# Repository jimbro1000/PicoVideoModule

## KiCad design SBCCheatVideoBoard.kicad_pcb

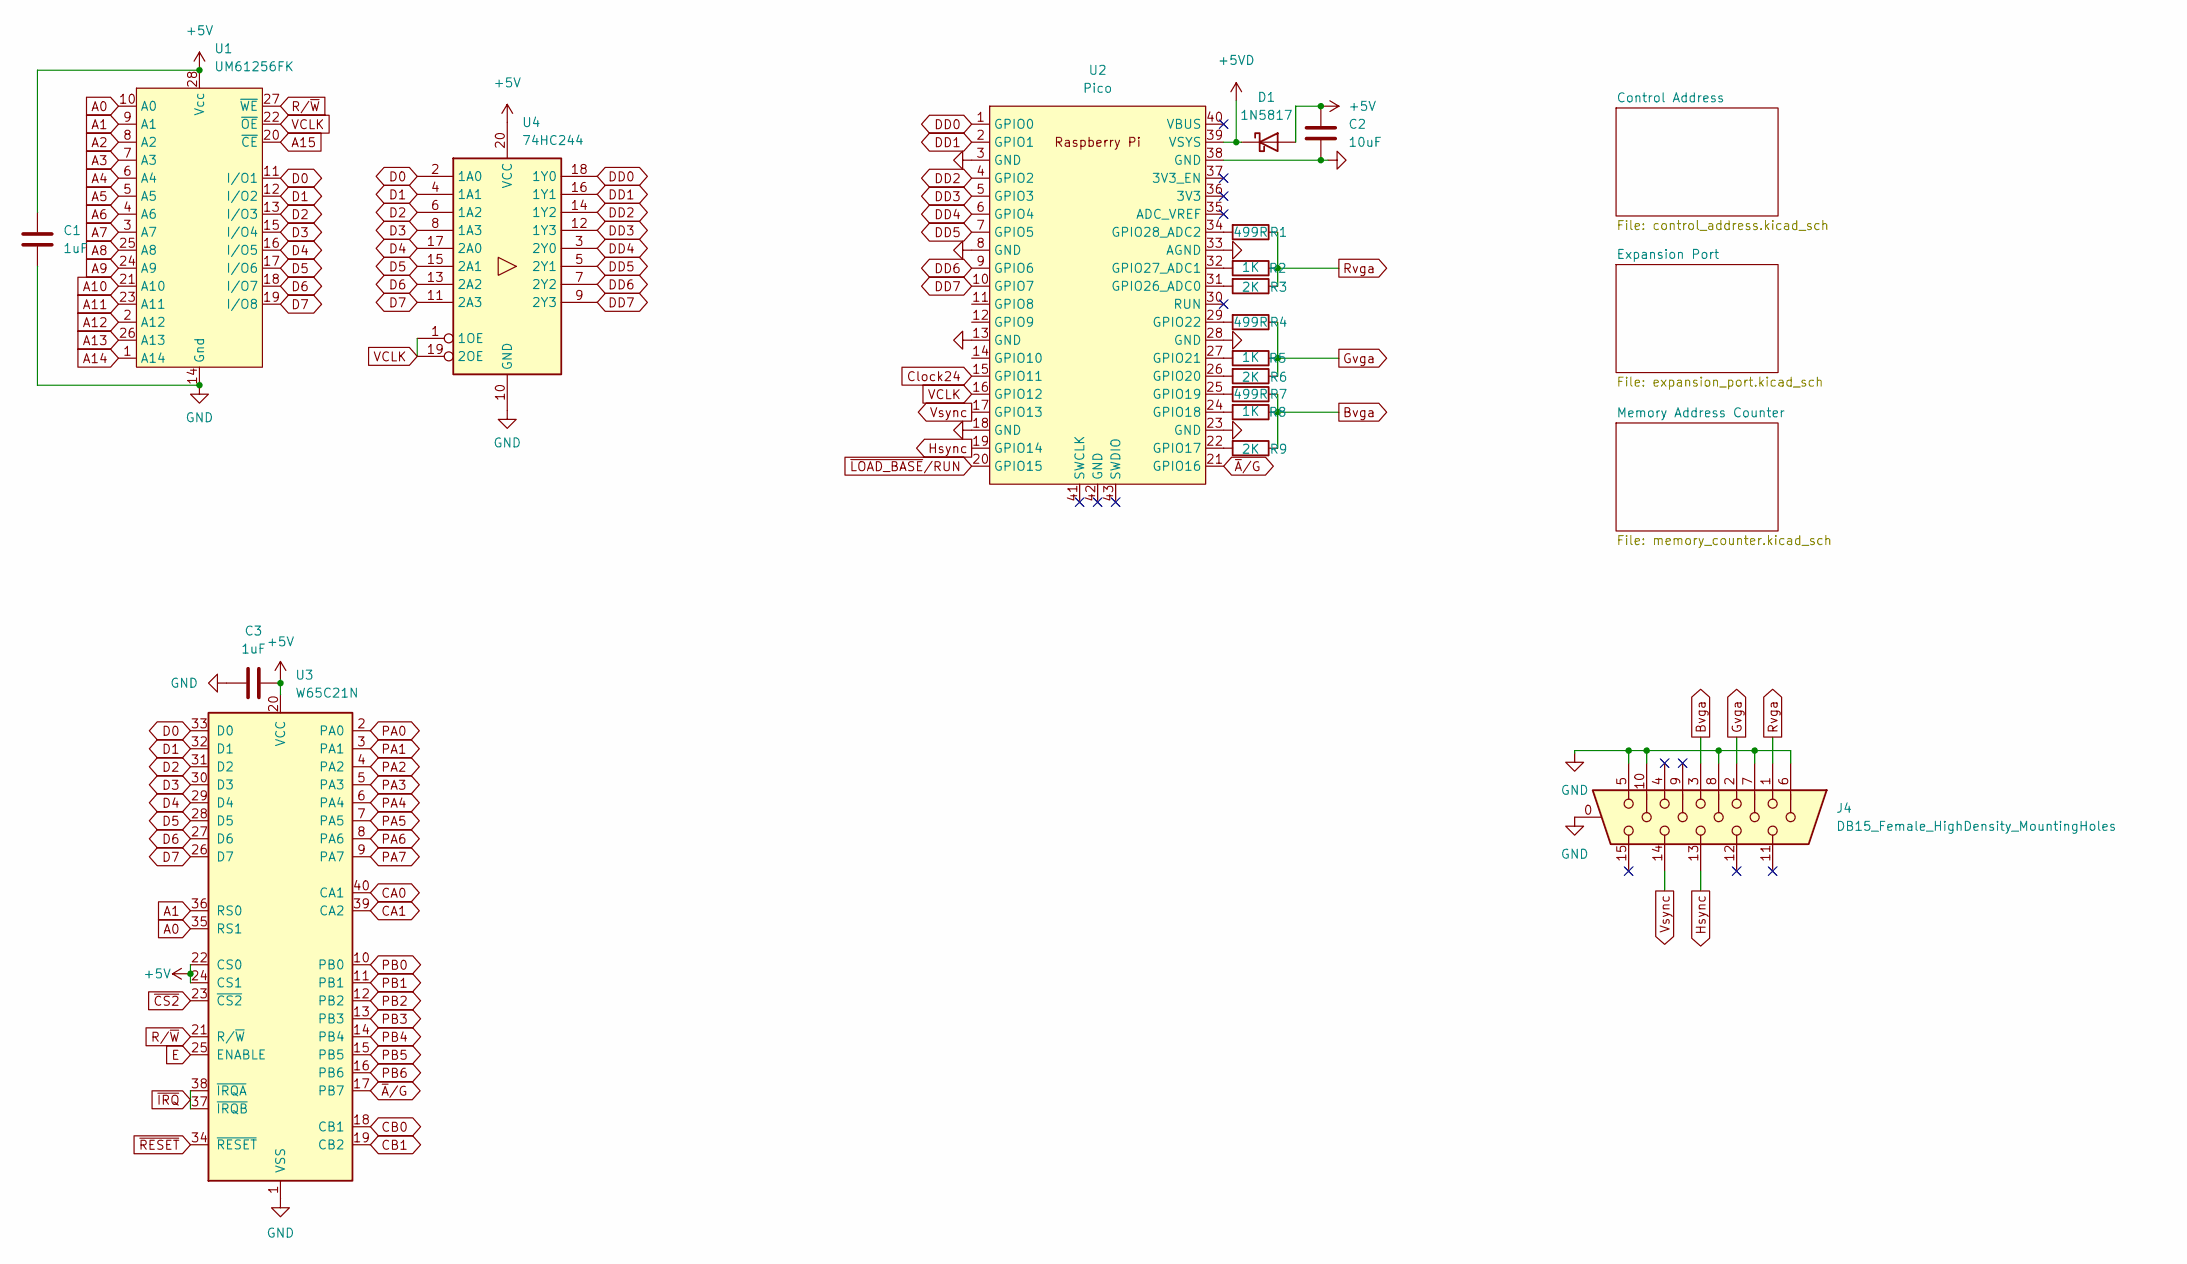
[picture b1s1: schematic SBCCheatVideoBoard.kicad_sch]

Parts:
C1, C3: 1uF; C_0805_2012Metric
C2: 10uF; C_0805_2012Metric
D1: 1N5817; D_SOD-523
J4: DB15_Female_HighDensity_MountingHoles; DSUB-15-HD_Female_Horizontal_P2.29x1.98mm_EdgePinOffset3.03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
R1, R4, R7: 499R; R_0805_2012Metric
R2, R5, R8: 1K; R_0805_2012Metric
R3, R6, R9: 2K; R_0805_2012Metric
U1: UM61256FK; DIP-28_W7.62mm
U2: Pico; DIP-40_W15.24mm
U3: W65C21N; DIP-40_W15.24mm
U4: 74HC244; SO-20_5.3x12.6mm_P1.27mm

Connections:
+5V: C1.1, C2.1, C3.1, D1.2 (A), U1.28 (Vcc), U3.20 (VCC), U3.22 (CS0), U3.24 (CS1), U4.20 (VCC); also elsewhere on the board
+5VD: D1.1 (K), U2.39 (VSYS)
A0: U1.10 (A0), U3.35 (RS1); also elsewhere on the board
A1: U1.9 (A1), U3.36 (RS0); also elsewhere on the board
A2: U1.8 (A2); also elsewhere on the board
A3: U1.7 (A3); also elsewhere on the board
A4: U1.6 (A4); also elsewhere on the board
A5: U1.5 (A5); also elsewhere on the board
A6: U1.4 (A6); also elsewhere on the board
A7: U1.3 (A7); also elsewhere on the board
A8: U1.25 (A8); also elsewhere on the board
A9: U1.24 (A9); also elsewhere on the board
A10: U1.21 (A10); also elsewhere on the board
A11: U1.23 (A11); also elsewhere on the board
A12: U1.2 (A12); also elsewhere on the board
A13: U1.26 (A13); also elsewhere on the board
A14: U1.1 (A14); also elsewhere on the board
A15: U1.20 (~CE); also elsewhere on the board
Bvga: J4.3, R7.1, R8.1, R9.1
CA0: U3.40 (CA1)
CA1: U3.39 (CA2)
CB0: U3.18 (CB1)
CB1: U3.19 (CB2)
Clock24: U2.15 (GPIO11); also elsewhere on the board
D0: U1.11 (I/O1), U3.33 (D0), U4.2 (1A0); also elsewhere on the board
D1: U1.12 (I/O2), U3.32 (D1), U4.4 (1A1); also elsewhere on the board
D2: U1.13 (I/O3), U3.31 (D2), U4.6 (1A2); also elsewhere on the board
D3: U1.15 (I/O4), U3.30 (D3), U4.8 (1A3); also elsewhere on the board
D4: U1.16 (I/O5), U3.29 (D4), U4.17 (2A0); also elsewhere on the board
D5: U1.17 (I/O6), U3.28 (D5), U4.15 (2A1); also elsewhere on the board
D6: U1.18 (I/O7), U3.27 (D6), U4.13 (2A2); also elsewhere on the board
D7: U1.19 (I/O8), U3.26 (D7), U4.11 (2A3); also elsewhere on the board
DD0: U2.1 (GPIO0), U4.18 (1Y0)
DD1: U2.2 (GPIO1), U4.16 (1Y1)
DD2: U2.4 (GPIO2), U4.14 (1Y2)
DD3: U2.5 (GPIO3), U4.12 (1Y3)
DD4: U2.6 (GPIO4), U4.3 (2Y0)
DD5: U2.7 (GPIO5), U4.5 (2Y1)
DD6: U2.9 (GPIO6), U4.7 (2Y2)
DD7: U2.10 (GPIO7), U4.9 (2Y3)
E: U3.25 (ENABLE); also elsewhere on the board
GND: C1.2, C2.2, C3.2, J4.0, J4.5, J4.6, J4.7, J4.8, J4.10, U1.14 (Gnd), U2.3 (GND), U2.8 (GND), U2.13 (GND), U2.18 (GND), U2.23 (GND), U2.28 (GND), U2.33 (AGND), U2.38 (GND), U3.1 (VSS), U4.10 (GND); also elsewhere on the board
Gvga: J4.2, R4.1, R5.1, R6.1
Hsync: J4.13, U2.19 (GPIO14)
unnamed: R1.2, U2.34 (GPIO28_ADC2)
unnamed: R2.2, U2.32 (GPIO27_ADC1)
unnamed: R3.2, U2.31 (GPIO26_ADC0)
unnamed: R4.2, U2.29 (GPIO22)
unnamed: R5.2, U2.27 (GPIO21)
unnamed: R6.2, U2.26 (GPIO20)
unnamed: R7.2, U2.25 (GPIO19)
unnamed: R8.2, U2.24 (GPIO18)
unnamed: R9.2, U2.22 (GPIO17)
PA0: U3.2 (PA0); also elsewhere on the board
PA1: U3.3 (PA1); also elsewhere on the board
PA2: U3.4 (PA2); also elsewhere on the board
PA3: U3.5 (PA3); also elsewhere on the board
PA4: U3.6 (PA4); also elsewhere on the board
PA5: U3.7 (PA5); also elsewhere on the board
PA6: U3.8 (PA6); also elsewhere on the board
PA7: U3.9 (PA7); also elsewhere on the board
PB0: U3.10 (PB0); also elsewhere on the board
PB1: U3.11 (PB1); also elsewhere on the board
PB2: U3.12 (PB2); also elsewhere on the board
PB3: U3.13 (PB3)
PB4: U3.14 (PB4)
PB5: U3.15 (PB5)
PB6: U3.16 (PB6)
Rvga: J4.1, R1.1, R2.1, R3.1
R/~W: U1.27 (~WE), U3.21 (R/~W); also elsewhere on the board
VCLK: U1.22 (~OE), U2.16 (GPIO12), U4.1 (1OE), U4.19 (2OE); also elsewhere on the board
Vsync: J4.14, U2.17 (GPIO13)
~A/G: U2.21 (GPIO16), U3.17 (PB7)
~CS2: U3.23 (~CS2); also elsewhere on the board
~IRQ: U3.37 (~IRQB), U3.38 (~IRQA); also elsewhere on the board
~LOAD_BASE/RUN: U2.20 (GPIO15); also elsewhere on the board
~RESET: U3.34 (~RESET); also elsewhere on the board

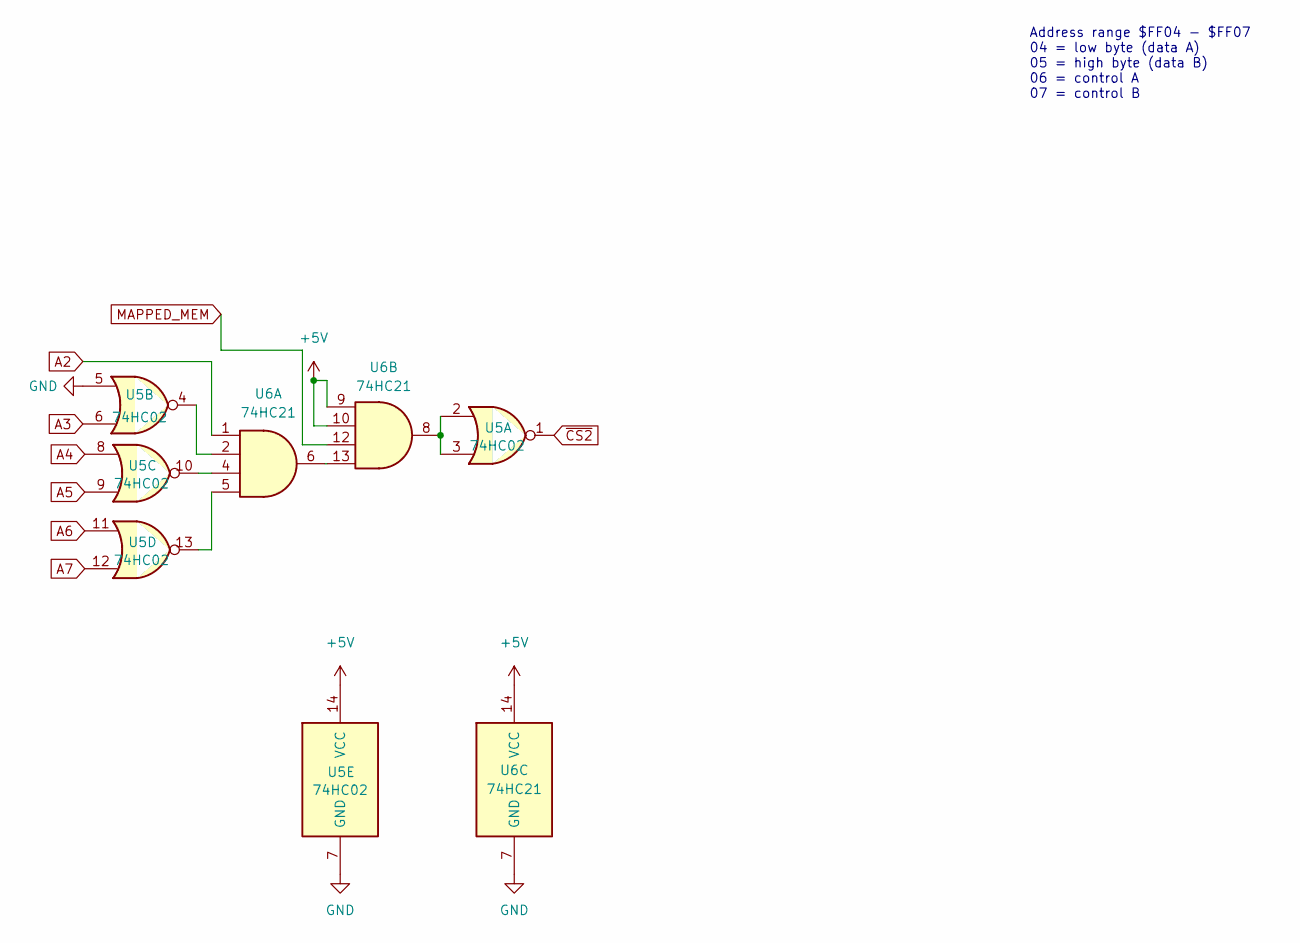
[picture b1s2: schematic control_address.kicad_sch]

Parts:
U5: 74HC02; SO-14_3.9x8.65mm_P1.27mm
U6: 74HC21; SO-14_3.9x8.65mm_P1.27mm

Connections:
+5V: U5.14 (VCC), U6.9, U6.10, U6.14 (VCC); also elsewhere on the board
A2: U6.1; also elsewhere on the board
A3: U5.6; also elsewhere on the board
A4: U5.8; also elsewhere on the board
A5: U5.9; also elsewhere on the board
A6: U5.11; also elsewhere on the board
A7: U5.12; also elsewhere on the board
GND: U5.5, U5.7 (GND), U6.7 (GND); also elsewhere on the board
MAPPED_MEM: U6.12; also elsewhere on the board
unnamed: U5.2, U5.3, U6.8
unnamed: U5.4, U6.2
unnamed: U5.10, U6.4
unnamed: U5.13, U6.5
unnamed: U6.6, U6.13
~CS2: U5.1; also elsewhere on the board

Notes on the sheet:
Address range $FF04 - $FF07 04 = low byte (data A) 05 = high byte (data B) 06 = control A 07 = control B

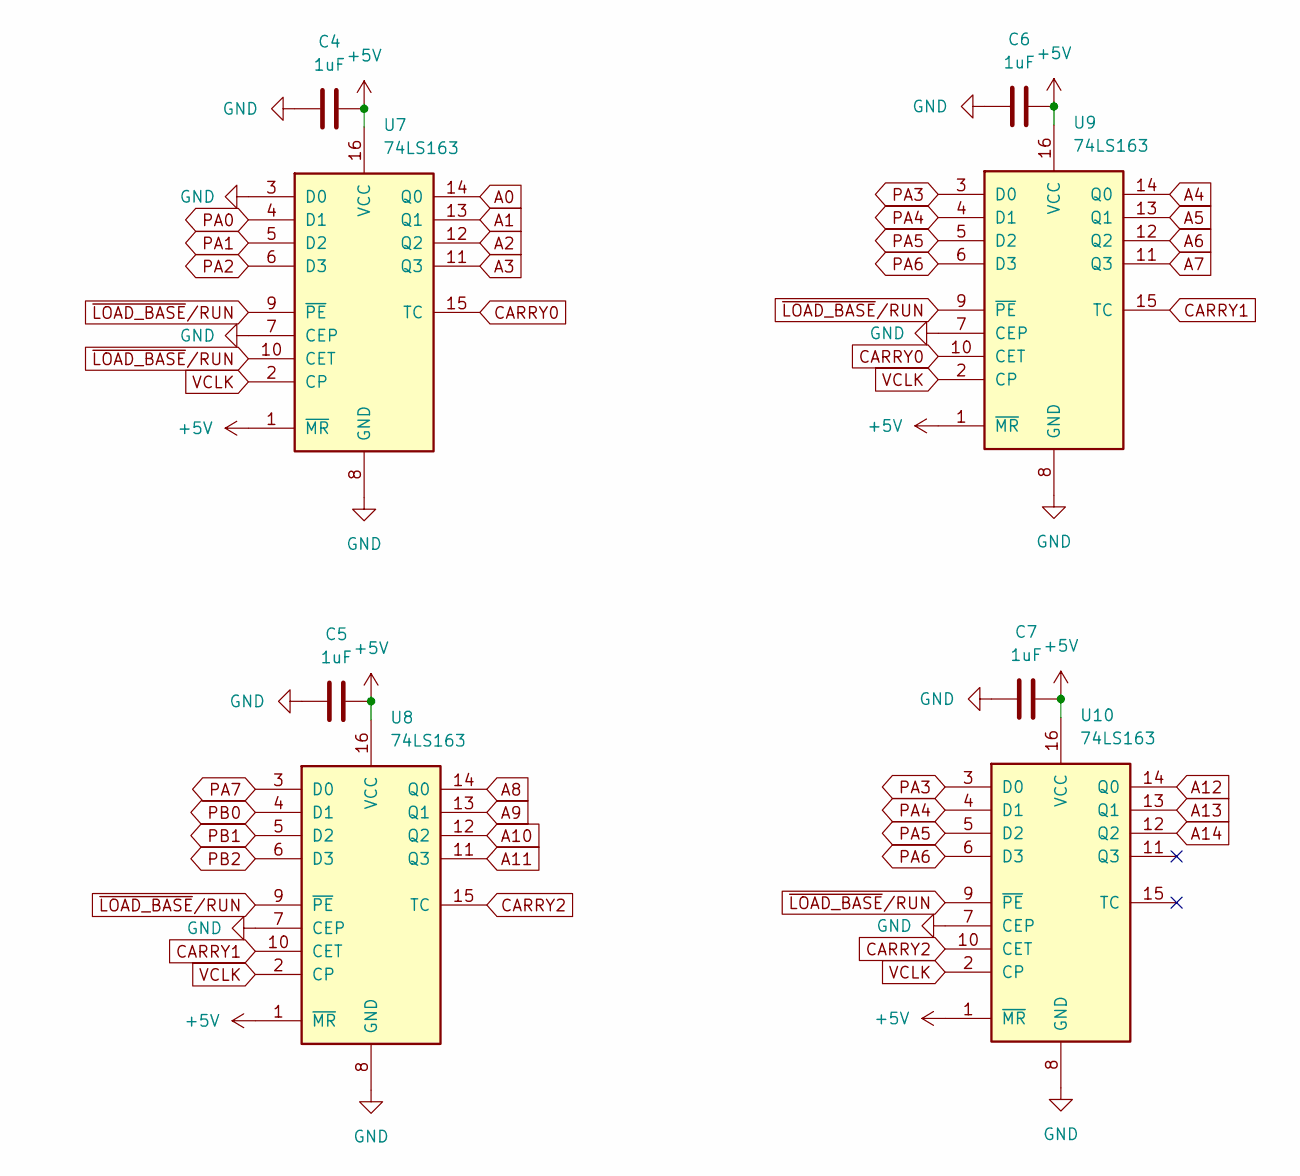
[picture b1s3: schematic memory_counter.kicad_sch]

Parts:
C4, C5, C6, C7: 1uF; C_0805_2012Metric
U7, U8, U9, U10: 74LS163; SO-16_3.9x9.9mm_P1.27mm

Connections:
+5V: C4.1, C5.1, C6.1, C7.1, U7.1 (~MR), U7.16 (VCC), U8.1 (~MR), U8.16 (VCC), U9.1 (~MR), U9.16 (VCC), U10.1 (~MR), U10.16 (VCC); also elsewhere on the board
A0: U7.14 (Q0); also elsewhere on the board
A1: U7.13 (Q1); also elsewhere on the board
A2: U7.12 (Q2); also elsewhere on the board
A3: U7.11 (Q3); also elsewhere on the board
A4: U9.14 (Q0); also elsewhere on the board
A5: U9.13 (Q1); also elsewhere on the board
A6: U9.12 (Q2); also elsewhere on the board
A7: U9.11 (Q3); also elsewhere on the board
A8: U8.14 (Q0); also elsewhere on the board
A9: U8.13 (Q1); also elsewhere on the board
A10: U8.12 (Q2); also elsewhere on the board
A11: U8.11 (Q3); also elsewhere on the board
A12: U10.14 (Q0); also elsewhere on the board
A13: U10.13 (Q1); also elsewhere on the board
A14: U10.12 (Q2); also elsewhere on the board
CARRY0: U7.15 (TC), U9.10 (CET)
CARRY1: U8.10 (CET), U9.15 (TC)
CARRY2: U8.15 (TC), U10.10 (CET)
GND: C4.2, C5.2, C6.2, C7.2, U7.3 (D0), U7.7 (CEP), U7.8 (GND), U8.7 (CEP), U8.8 (GND), U9.7 (CEP), U9.8 (GND), U10.7 (CEP), U10.8 (GND); also elsewhere on the board
PA0: U7.4 (D1); also elsewhere on the board
PA1: U7.5 (D2); also elsewhere on the board
PA2: U7.6 (D3); also elsewhere on the board
PA3: U9.3 (D0), U10.3 (D0); also elsewhere on the board
PA4: U9.4 (D1), U10.4 (D1); also elsewhere on the board
PA5: U9.5 (D2), U10.5 (D2); also elsewhere on the board
PA6: U9.6 (D3), U10.6 (D3); also elsewhere on the board
PA7: U8.3 (D0); also elsewhere on the board
PB0: U8.4 (D1); also elsewhere on the board
PB1: U8.5 (D2); also elsewhere on the board
PB2: U8.6 (D3); also elsewhere on the board
VCLK: U7.2 (CP), U8.2 (CP), U9.2 (CP), U10.2 (CP); also elsewhere on the board
~LOAD_BASE/RUN: U7.9 (~PE), U7.10 (CET), U8.9 (~PE), U9.9 (~PE), U10.9 (~PE); also elsewhere on the board

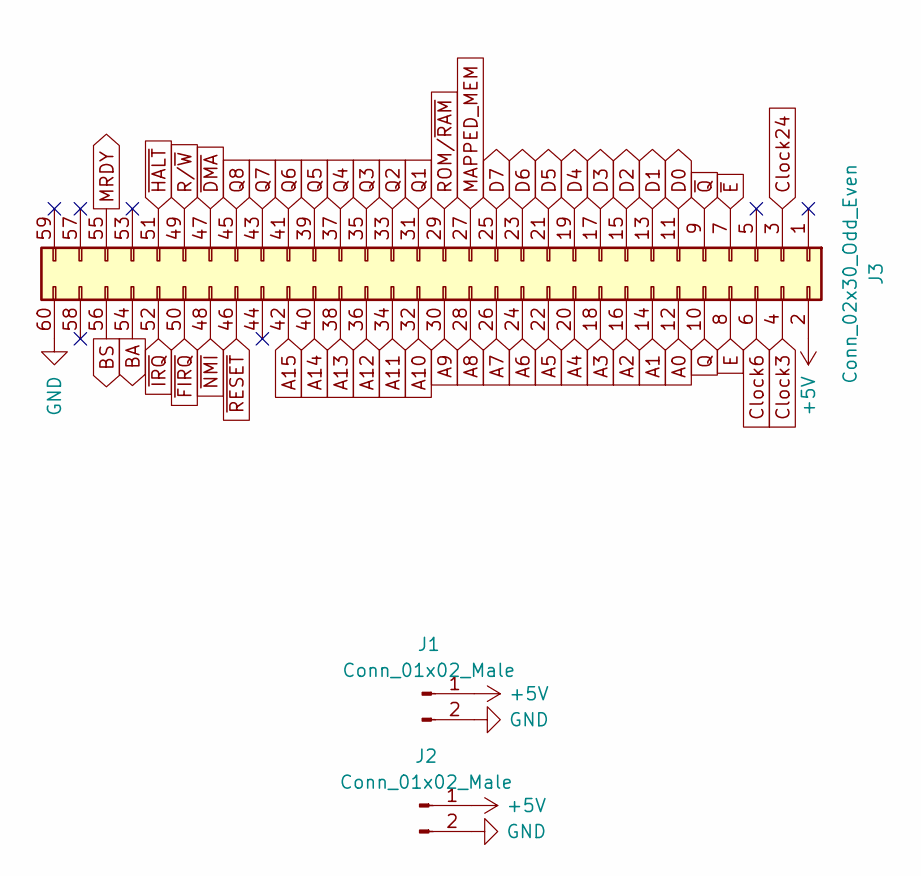
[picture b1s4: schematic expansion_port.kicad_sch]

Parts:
J1, J2: Conn_01x02_Male; PinHeader_1x02_P2.54mm_Vertical
J3: Conn_02x30_Odd_Even; PinHeader_2x30_P2.54mm_Vertical

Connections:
+5V: J1.1, J2.1, J3.2; also elsewhere on the board
A0: J3.12; also elsewhere on the board
A1: J3.14; also elsewhere on the board
A2: J3.16; also elsewhere on the board
A3: J3.18; also elsewhere on the board
A4: J3.20; also elsewhere on the board
A5: J3.22; also elsewhere on the board
A6: J3.24; also elsewhere on the board
A7: J3.26; also elsewhere on the board
A8: J3.28; also elsewhere on the board
A9: J3.30; also elsewhere on the board
A10: J3.32; also elsewhere on the board
A11: J3.34; also elsewhere on the board
A12: J3.36; also elsewhere on the board
A13: J3.38; also elsewhere on the board
A14: J3.40; also elsewhere on the board
A15: J3.42; also elsewhere on the board
BA: J3.54
BS: J3.56
Clock3: J3.4
Clock6: J3.6
Clock24: J3.3; also elsewhere on the board
D0: J3.11; also elsewhere on the board
D1: J3.13; also elsewhere on the board
D2: J3.15; also elsewhere on the board
D3: J3.17; also elsewhere on the board
D4: J3.19; also elsewhere on the board
D5: J3.21; also elsewhere on the board
D6: J3.23; also elsewhere on the board
D7: J3.25; also elsewhere on the board
E: J3.8; also elsewhere on the board
GND: J1.2, J2.2, J3.60; also elsewhere on the board
MAPPED_MEM: J3.27; also elsewhere on the board
MRDY: J3.55
Q: J3.10
Q1: J3.31
Q2: J3.33
Q3: J3.35
Q4: J3.37
Q5: J3.39
Q6: J3.41
Q7: J3.43
Q8: J3.45
ROM/~RAM: J3.29
R/~W: J3.49; also elsewhere on the board
~DMA: J3.47
~E: J3.7
~FIRQ: J3.50
~HALT: J3.51
~IRQ: J3.52; also elsewhere on the board
~NMI: J3.48
~Q: J3.9
~RESET: J3.46; also elsewhere on the board

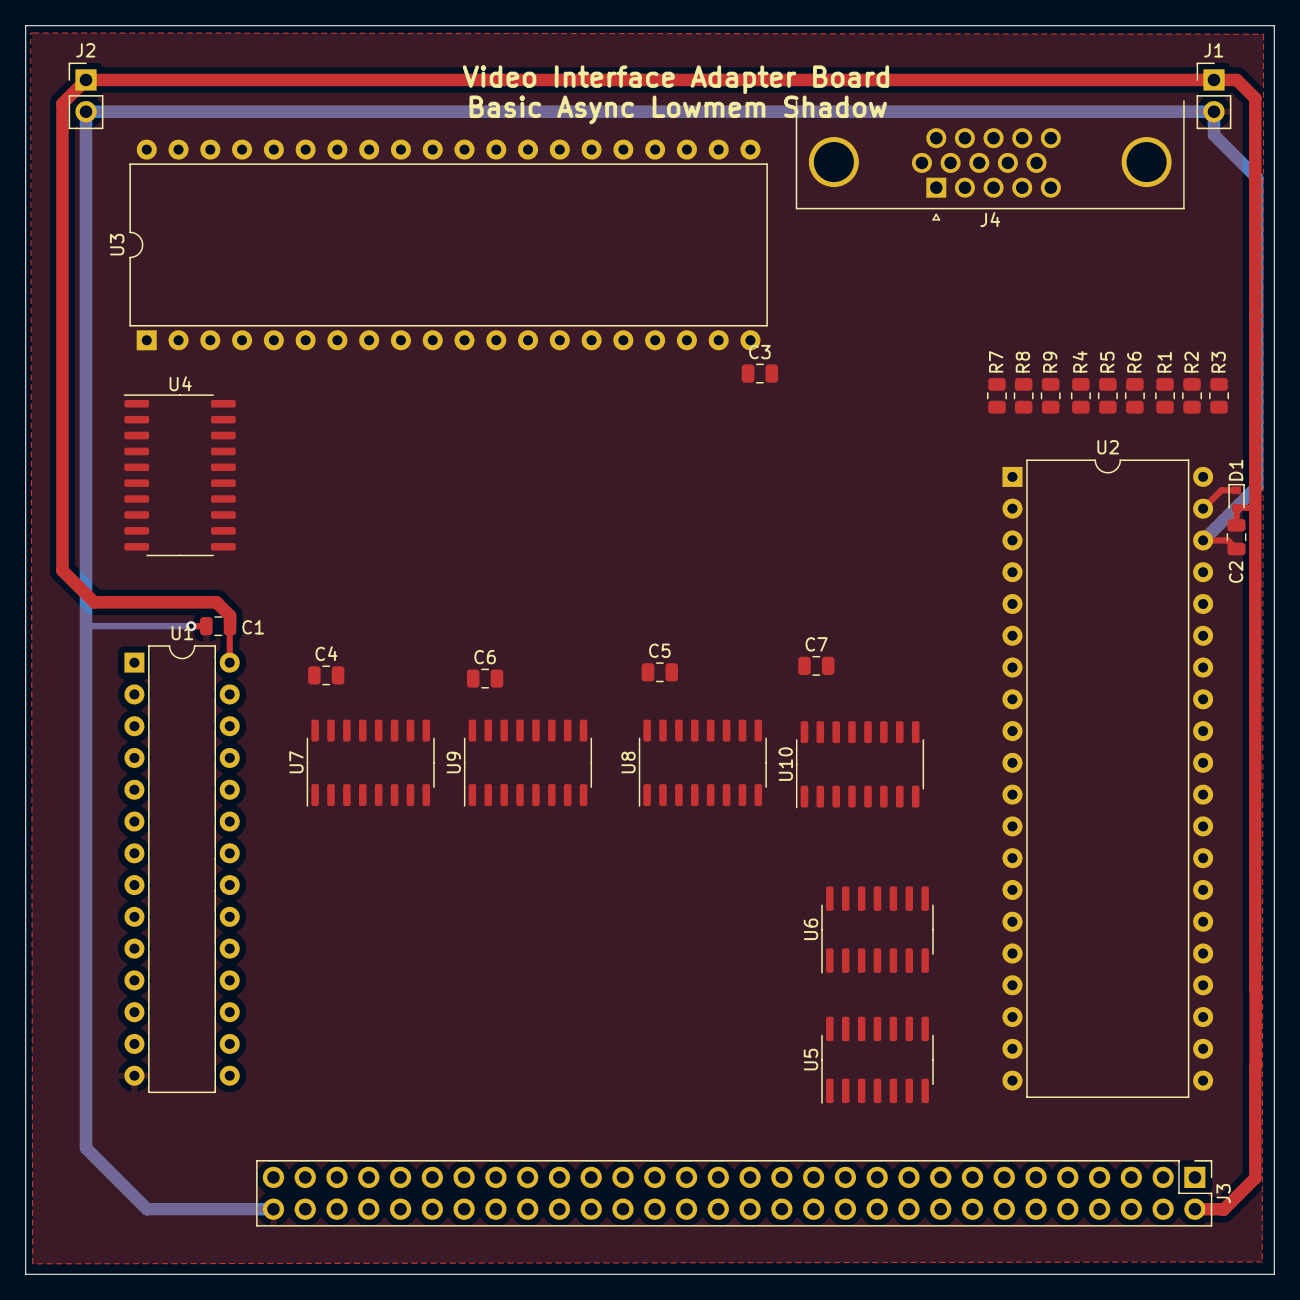
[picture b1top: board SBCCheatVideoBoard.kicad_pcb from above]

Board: 2 copper layers, 99.8 x 99.8 mm, 31 parts (0 on the bottom side), 78 nets.
